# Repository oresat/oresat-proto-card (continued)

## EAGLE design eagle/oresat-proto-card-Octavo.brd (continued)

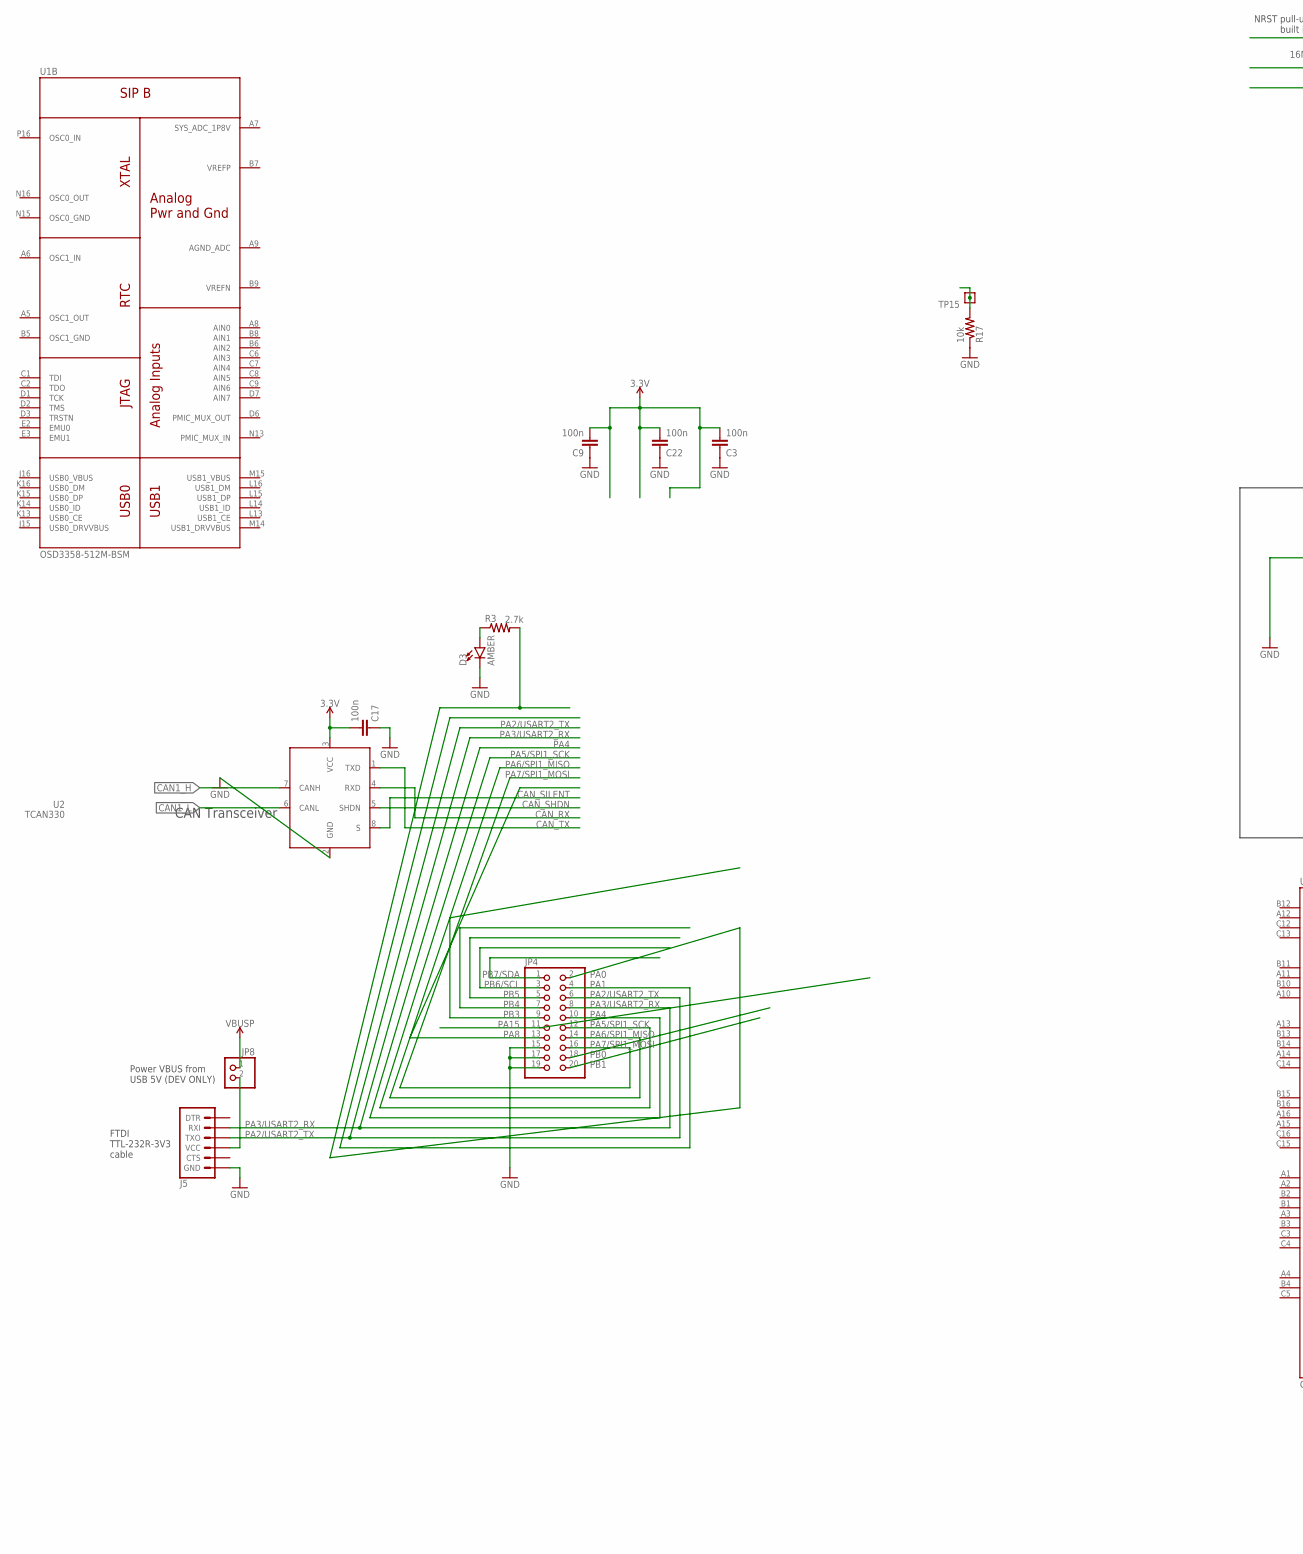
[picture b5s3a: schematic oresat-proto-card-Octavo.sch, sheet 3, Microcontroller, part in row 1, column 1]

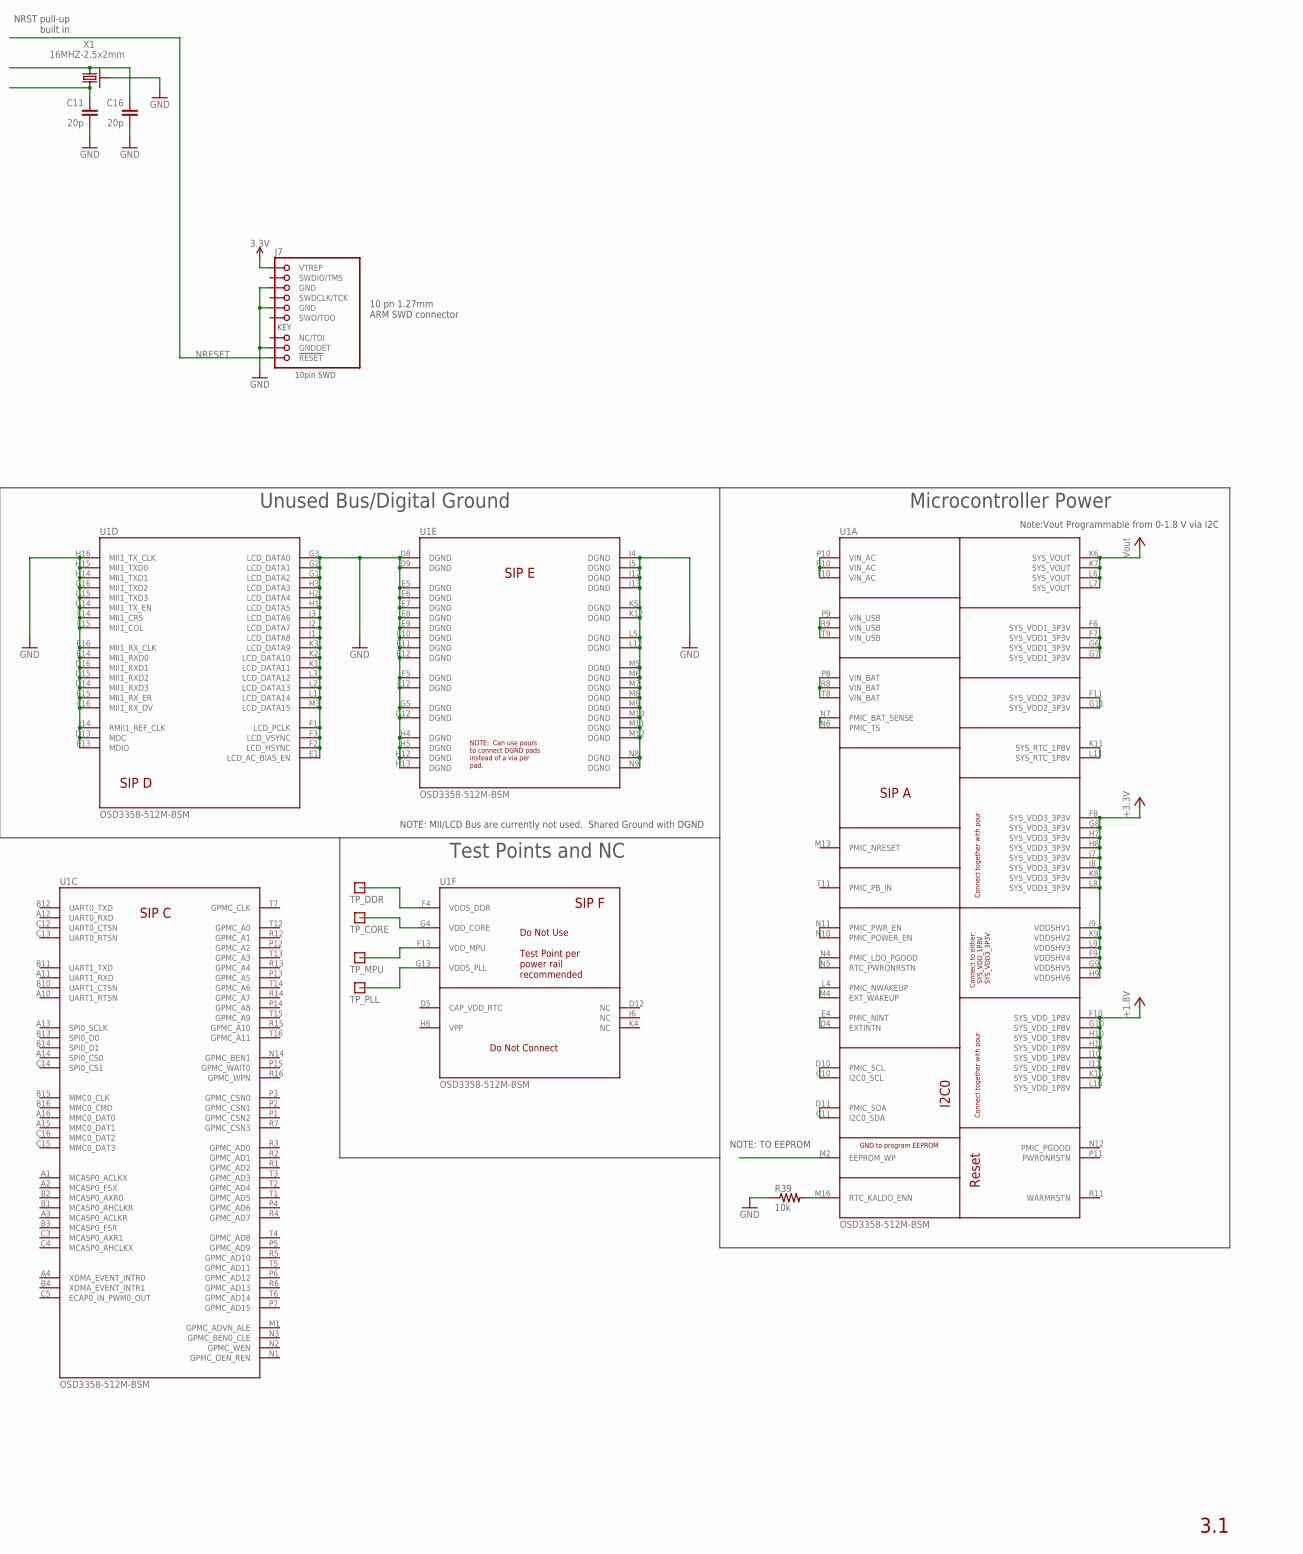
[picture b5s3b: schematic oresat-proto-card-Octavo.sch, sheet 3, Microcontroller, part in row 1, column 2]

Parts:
C3, C9, C17, C22: 100n; .0402-B-NOSILK; MPN CL05B104KO5NNNC
C11, C16: 20p; .0402-B-NOSILK; MPN CL05C200JB51PNC
D3: AMBER; LED-0603
J5: 6_PIN_SERIAL_TARGETSILK; 6_PIN_SERIAL_TARGET_SIDE_W_SILK
J7: FTSH-105-XX-X-DV-K; CON10_2X5_DUK_FTSH; MPN FTSH-105-01-F-DV-K
JP4: PINHD-2X10; 2X10
JP8: PINHD-1X2; 1X02
R3: 2.7k; .0402-B-NOSILK; MPN RC1005F6653CS
R17: 10k; .0402-B-NOSILK; MPN RC1005F6653CS
R39: 10k; R0201
TP15: TEST-POINT; 2MM-TEST-POINT
TP_CORE: TEST-POINT; 2MM-TEST-POINT
TP_DDR: TEST-POINT; 2MM-TEST-POINT
TP_MPU: TEST-POINT; 2MM-TEST-POINT
TP_PLL: TEST-POINT; 2MM-TEST-POINT
U1: OSD3358-512M-BSM; OSD335X-BGA-256
U2: TCAN330; SOT23-8_TI-DCN; MPN TCAN330GDCNT
X1: 16MHZ-2.5x2mm; CRYSTAL_2.5X2; MPN ECS-160-10-36Q-ES-TR

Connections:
3.3V: C3.2, C9.2, C17.2, C22.2, J7.1 (VTREF), U2.3 (VCC); also elsewhere on the board
+3V3: U1.F8 (SYS_VDD3_3P3V), U1.F9 (VDDSHV4), U1.F10 (SYS_VDD_1P8V), U1.G8 (SYS_VDD3_3P3V), U1.G9 (VDDSHV5), U1.G10 (SYS_VDD_1P8V), U1.H7 (SYS_VDD3_3P3V), U1.H8 (SYS_VDD3_3P3V), U1.H9 (VDDSHV6), U1.H10 (SYS_VDD_1P8V), U1.H11 (SYS_VDD_1P8V), U1.J7 (SYS_VDD3_3P3V), U1.J8 (SYS_VDD3_3P3V), U1.J9 (VDDSHV1), U1.J10 (SYS_VDD_1P8V), U1.J11 (SYS_VDD_1P8V), U1.K8 (SYS_VDD3_3P3V), U1.K9 (VDDSHV2), U1.K10 (SYS_VDD_1P8V), U1.L8 (SYS_VDD3_3P3V), U1.L9 (VDDSHV3), U1.L10 (SYS_VDD_1P8V)
BOOT: R17.2, TP15.1
CAN1_H: U2.7 (CANH); also elsewhere on the board
CAN1_L: U2.6 (CANL); also elsewhere on the board
CAN_RX: U2.4 (RXD)
CAN_SHDN: U2.5 (SHDN)
CAN_SILENT: U2.8 (S)
CAN_TX: U2.1 (TXD)
CRYSTALIN: C16.1, X1.1
CRYSTALOUT: C11.1, X1.3 (2)
GND: C3.1, C9.1, C11.2, C16.2, C17.1, C22.1, D3.C, J5.P$6 (GND), J7.3 (GND), J7.5 (GND), J7.9 (GNDDET), JP4.15, JP4.17, JP4.19, R17.1, R39.1, U1.D8 (DGND), U1.D9 (DGND), U1.D13 (MDC), U1.D14 (MII1_RXD3), U1.D15 (MII1_RXD2), U1.D16 (MII1_RXD1), U1.E1 (LCD_AC_BIAS_EN), U1.E5 (DGND), U1.E6 (DGND), U1.E7 (DGND), U1.E8 (DGND), U1.E9 (DGND), U1.E10 (DGND), U1.E11 (DGND), U1.E12 (DGND), U1.E13 (MDIO), U1.E14 (MII1_RXD0), U1.E15 (MII1_RX_ER), U1.E16 (MII1_RX_CLK), U1.F1 (LCD_PCLK), U1.F2 (LCD_HSYNC), U1.F3 (LCD_VSYNC), U1.F5 (DGND), U1.F12 (DGND), U1.F14 (MII1_CRS), U1.F15 (MII1_COL), U1.F16 (MII1_RX_DV), U1.G1 (LCD_DATA2), U1.G2 (LCD_DATA1), U1.G3 (LCD_DATA0), U1.G5 (DGND), U1.G12 (DGND), U1.G14 (MII1_TX_EN), U1.G15 (MII1_TXD3), U1.G16 (MII1_TXD2), U1.H1 (LCD_DATA5), U1.H2 (LCD_DATA4), U1.H3 (LCD_DATA3), U1.H4 (DGND), U1.H5 (DGND), U1.H12 (DGND), U1.H13 (DGND), U1.H14 (MII1_TXD1), U1.H15 (MII1_TXD0), U1.H16 (MII1_TX_CLK), U1.J1 (LCD_DATA8), U1.J2 (LCD_DATA7), U1.J3 (LCD_DATA6), U1.J4 (DGND), U1.J5 (DGND), U1.J12 (DGND), U1.J13 (DGND), U1.J14 (RMII1_REF_CLK), U1.K1 (LCD_DATA11), U1.K2 (LCD_DATA10), U1.K3 (LCD_DATA9), U1.K5 (DGND), U1.K12 (DGND), U1.L1 (LCD_DATA14), U1.L2 (LCD_DATA13), U1.L3 (LCD_DATA12), U1.L5 (DGND), U1.L12 (DGND), U1.M3 (LCD_DATA15), U1.M5 (DGND), U1.M6 (DGND), U1.M7 (DGND), U1.M8 (DGND), U1.M9 (DGND), U1.M10 (DGND), U1.M11 (DGND), U1.M12 (DGND), U1.N8 (DGND), U1.N9 (DGND), U2.2 (GND), X1.2 (SHIELD), X1.4 (SHIELD); also elsewhere on the board
unnamed: D3.A, R3.1
unnamed: U1.F11 (SYS_VDD2_3P3V), U1.G11 (SYS_VDD2_3P3V)
unnamed: U1.N6 (PMIC_TS), U1.N7 (PMIC_BAT_SENSE)
unnamed: U1.K11 (SYS_RTC_1P8V), U1.L11 (SYS_RTC_1P8V)
unnamed: U1.D4 (EXTINTN), U1.E4 (PMIC_NINT)
unnamed: U1.F6 (SYS_VDD1_3P3V), U1.F7 (SYS_VDD1_3P3V), U1.G6 (SYS_VDD1_3P3V), U1.G7 (SYS_VDD1_3P3V)
unnamed: U1.K6 (SYS_VOUT), U1.K7 (SYS_VOUT), U1.L6 (SYS_VOUT), U1.L7 (SYS_VOUT)
unnamed: U1.P10 (VIN_AC), U1.R10 (VIN_AC), U1.T10 (VIN_AC)
unnamed: U1.P9 (VIN_USB), U1.R9 (VIN_USB), U1.T9 (VIN_USB)
unnamed: U1.P8 (VIN_BAT), U1.R8 (VIN_BAT), U1.T8 (VIN_BAT)
unnamed: U1.L4 (PMIC_NWAKEUP), U1.M4 (EXT_WAKEUP)
unnamed: U1.N4 (PMIC_LDO_PGOOD), U1.N5 (RTC_PWRONRSTN)
unnamed: U1.N10 (PMIC_POWER_EN), U1.N11 (PMIC_PWR_EN)
unnamed: U1.C10 (I2C0_SCL), U1.D10 (PMIC_SCL)
unnamed: U1.C11 (I2C0_SDA), U1.D11 (PMIC_SDA)
unnamed: TP_MPU.1, U1.F13 (VDD_MPU)
unnamed: R39.2, U1.M16 (RTC_KALDO_ENN)
unnamed: TP_PLL.1, U1.G13 (VDDS_PLL)
unnamed: TP_CORE.1, U1.G4 (VDD_CORE)
unnamed: TP_DDR.1, U1.F4 (VDDS_DDR)
unnamed: J5.P$4 (VCC), JP8.2
NRESET: J7.10 (!RESET)
PA0: JP4.2, R3.2
PA1: JP4.4
PA2/USART2_TX: J5.P$2 (TXO), JP4.6
PA3/USART2_RX: J5.P$3 (RXI), JP4.8
PA4: JP4.10
PA5/SPI1_SCK: JP4.12
PA6/SPI1_MISO: JP4.14
PA7/SPI1_MOSI: JP4.16
PA8: JP4.13
PA15: JP4.11
PB0: JP4.18
PB1: JP4.20
PB3: JP4.9
PB4: JP4.7
PB5: JP4.5
PB6/SCL: JP4.3
PB7/SDA: JP4.1
VBUSP: JP8.1; also elsewhere on the board

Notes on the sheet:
NRST pull-up built in
FTDI TTL-232R-3V3 cable
Power VBUS from USB 5V (DEV ONLY)
10 pn 1.27mm ARM SWD connector
CAN Transceiver
3.1
NOTE: TO EEPROM
Note:Vout Programmable from 0-1.8 V via I2C
Microcontroller Power
NOTE: MII/LCD Bus are currently not used. Shared Ground with DGND
Unused Bus/Digital Ground
Test Points and NC

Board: 4 copper layers, 118 parts (0 on the bottom side), 96 nets, no tracks yet.

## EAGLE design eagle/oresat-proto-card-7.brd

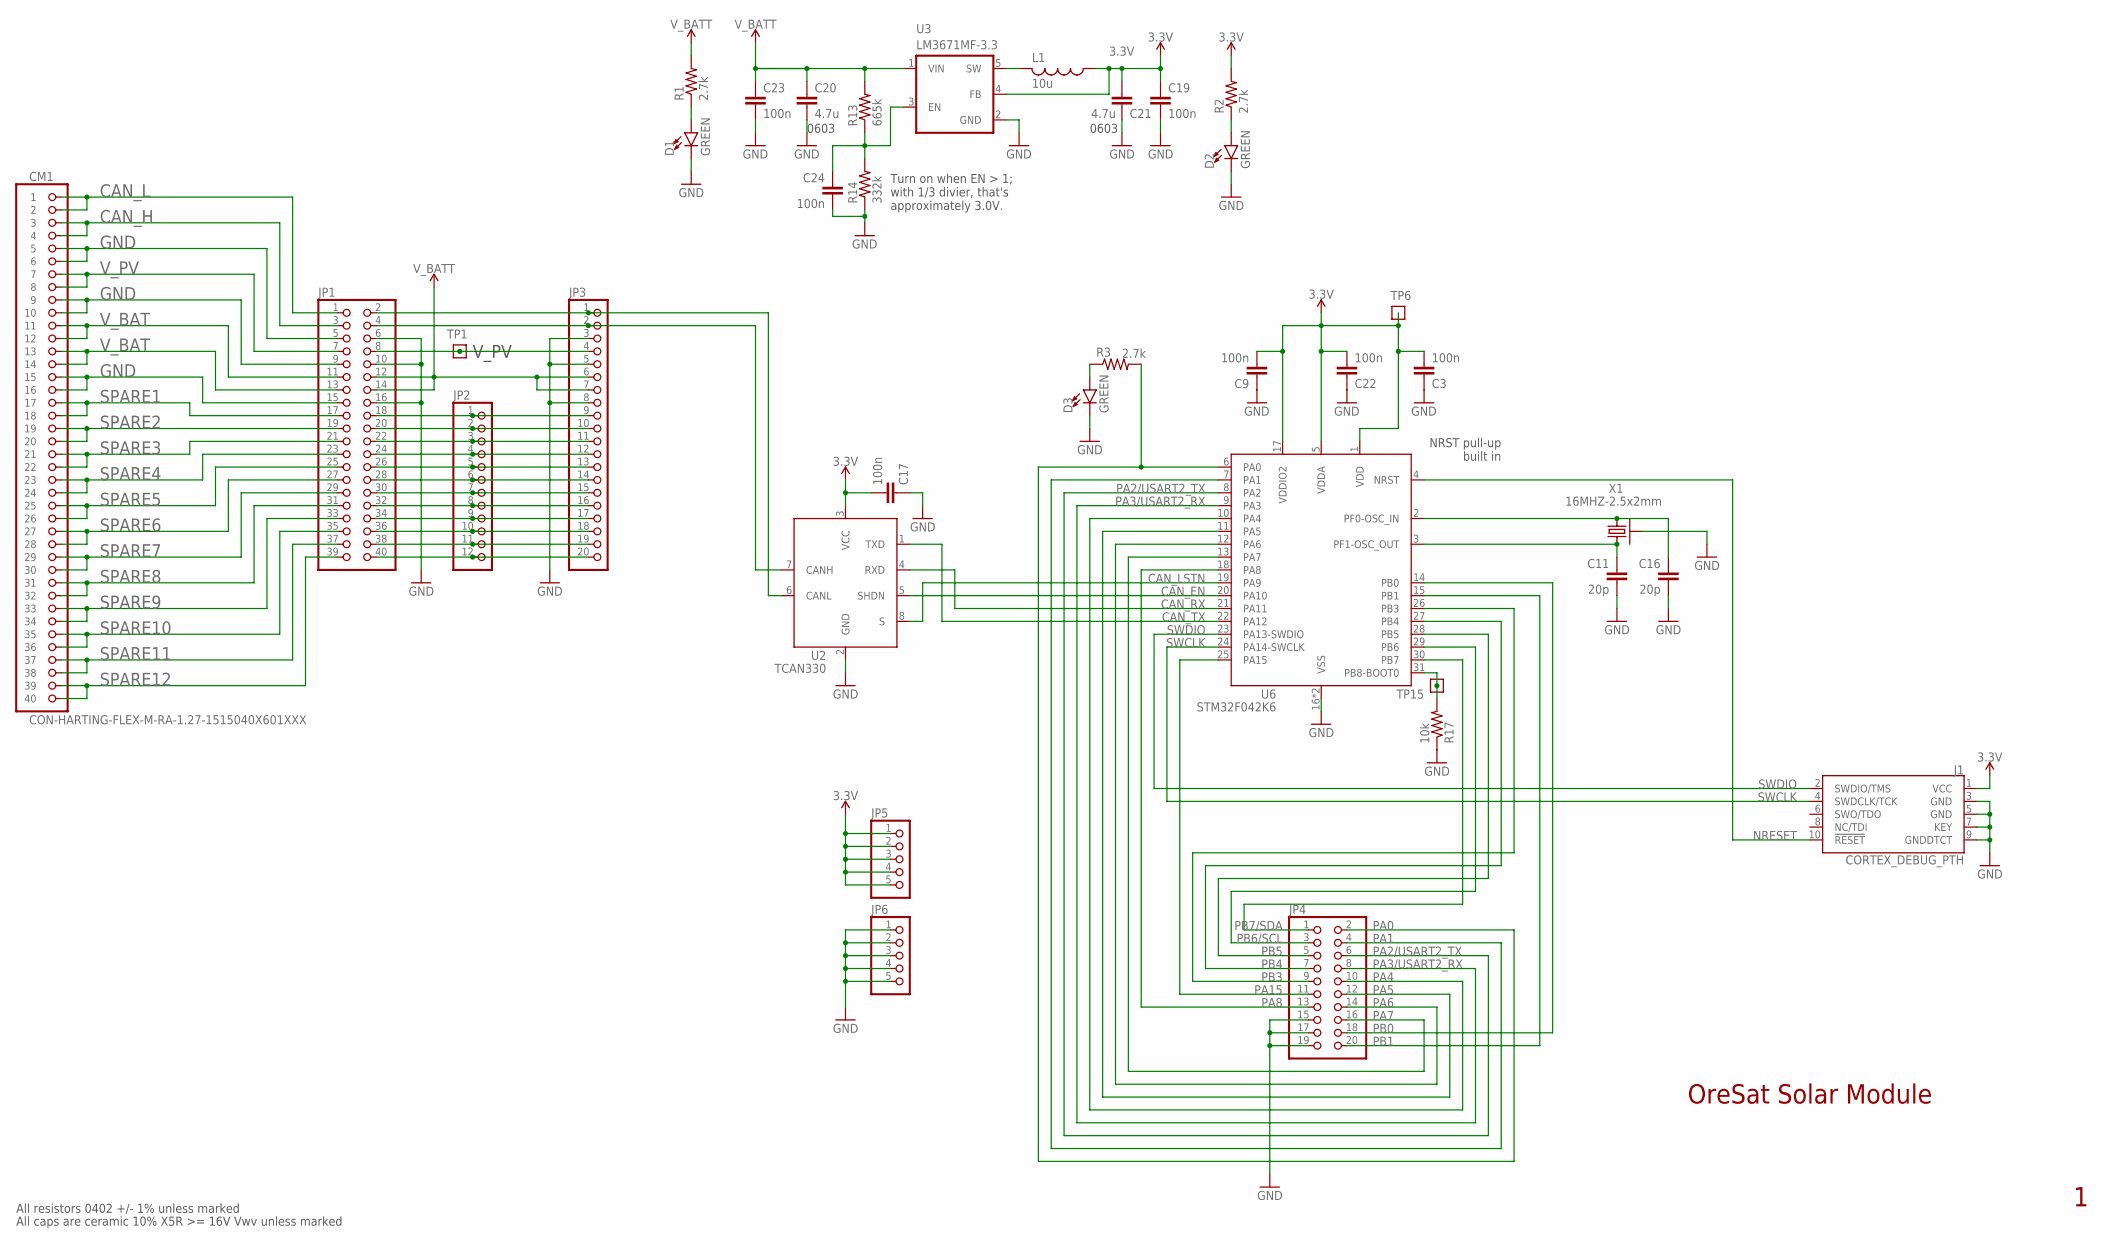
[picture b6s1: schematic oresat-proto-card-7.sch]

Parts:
C3, C9, C17, C19, C22, C23, C24: 100n; .0402-B-NOSILK; MPN CL05B104KO5NNNC
C11, C16: 20p; .0402-B-NOSILK; MPN CL05C200JB51PNC
C20, C21: 4.7u; C0603; MPN CL05B104KO5NNNC
CM1: CON-HARTING-FLEX-M-RA-1.27-1515040X601XXX; CON-1.27-M-RA-HARTING-1515040X601XXX
D1, D2, D3: GREEN; LED-0603
J1: CORTEX_DEBUG_PTH; 2X5-PTH-1.27MM
JP1: PINHD-2X20; 2X20
JP2: PINHD-1X12; 1X12
JP3: PINHD-1X20; 1X20
JP4: PINHD-2X10; 2X10
JP5, JP6: PINHD-1X5; 1X05
L1: 10u; L2012C; MPN CB2012T100KR
R1, R2, R3: 2.7k; .0402-B-NOSILK; MPN RC1005F6653CS
R13: 665k; .0402-B-NOSILK; MPN RC1005F6653CS
R14: 332k; .0402-B-NOSILK; MPN RC1005F3323CS
R17: 10k; .0402-B-NOSILK; MPN RC1005F6653CS
TP1, TP6, TP15: TEST-POINT; 2MM-TEST-POINT
U2: TCAN330; SOT23-8_TI-DCN; MPN TCAN330GDCNT
U3: LM3671MF-3.3; SOT23-5; MPN LM3671MF-3.3/NOPB
U6: STM32F042K6; QFP32-7X7; MPN STM32F042K6T7
X1: 16MHZ-2.5x2mm; CRYSTAL_2.5X2; MPN ECS-160-10-36Q-ES-TR

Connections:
3.3V: C3.2, C9.2, C17.2, C19.1, C21.1, C22.2, J1.1 (VCC), JP5.1, JP5.2, JP5.3, JP5.4, JP5.5, L1.1, R2.2, TP6.1, U2.3 (VCC), U3.4 (FB), U6.1 (VDD), U6.5 (VDDA), U6.17 (VDDIO2)
BOOT: R17.2, TP15.1, U6.31 (PB8-BOOT0)
CANH: JP1.4, JP3.2, U2.7 (CANH)
CANL: JP1.2, JP3.1, U2.6 (CANL)
CAN_EN: U2.5 (SHDN), U6.20 (PA10)
CAN_H: CM1.3, CM1.4, JP1.3
CAN_L: CM1.1, CM1.2, JP1.1
CAN_LSTN: U2.8 (S), U6.19 (PA9)
CAN_RX: U2.4 (RXD), U6.21 (PA11)
CAN_TX: U2.1 (TXD), U6.22 (PA12)
CRYSTALIN: C16.1, U6.2 (PF0-OSC_IN), X1.1
CRYSTALOUT: C11.1, U6.3 (PF1-OSC_OUT), X1.3 (2)
GND: C3.1, C9.1, C11.2, C16.2, C17.1, C19.2, C20.2, C21.2, C22.1, C23.2, C24.2, CM1.5, CM1.6, CM1.9, CM1.10, CM1.15, CM1.16, D1.C, D2.C, D3.C, J1.3 (GND), J1.5 (GND), J1.7 (KEY), J1.9 (GNDDTCT), JP1.5, JP1.6, JP1.9, JP1.10, JP1.15, JP1.16, JP3.3, JP3.5, JP3.8, JP4.15, JP4.17, JP4.19, JP6.1, JP6.2, JP6.3, JP6.4, JP6.5, R14.1, R17.1, U2.2 (GND), U3.2 (GND), U6.16 (VSS), U6.32 (VSS), X1.2 (SHIELD), X1.4 (SHIELD)
unnamed: D3.A, R3.1
unnamed: JP1.8, JP3.4, TP1.1
unnamed: JP1.18, JP2.1, JP3.9
unnamed: JP1.20, JP2.2, JP3.10
unnamed: JP1.22, JP2.3, JP3.11
unnamed: JP1.24, JP2.4, JP3.12
unnamed: JP1.26, JP2.5, JP3.13
unnamed: JP1.28, JP2.6, JP3.14
unnamed: JP1.30, JP2.7, JP3.15
unnamed: JP1.32, JP2.8, JP3.16
unnamed: JP1.34, JP2.9, JP3.17
unnamed: JP1.36, JP2.10, JP3.18
unnamed: JP1.38, JP2.11, JP3.19
unnamed: JP1.40, JP2.12, JP3.20
unnamed: D1.A, R1.1
unnamed: D2.A, R2.1
NRESET: J1.10 (!RESET), U6.4 (NRST)
PA0: JP4.2, R3.2, U6.6 (PA0)
PA1: JP4.4, U6.7 (PA1)
PA2/USART2_TX: JP4.6, U6.8 (PA2)
PA3/USART2_RX: JP4.8, U6.9 (PA3)
PA4: JP4.10, U6.10 (PA4)
PA5: JP4.12, U6.11 (PA5)
PA6: JP4.14, U6.12 (PA6)
PA7: JP4.16, U6.13 (PA7)
PA8: JP4.13, U6.18 (PA8)
PA15: JP4.11, U6.25 (PA15)
PB0: JP4.18, U6.14 (PB0)
PB1: JP4.20, U6.15 (PB1)
PB3: JP4.9, U6.26 (PB3)
PB4: JP4.7, U6.27 (PB4)
PB5: JP4.5, U6.28 (PB5)
PB6/SCL: JP4.3, U6.29 (PB6)
PB7/SDA: JP4.1, U6.30 (PB7)
SPARE1: CM1.17, CM1.18, JP1.17
SPARE2: CM1.19, CM1.20, JP1.19
SPARE3: CM1.21, CM1.22, JP1.21
SPARE4: CM1.23, CM1.24, JP1.23
SPARE5: CM1.25, CM1.26, JP1.25
SPARE6: CM1.27, CM1.28, JP1.27
SPARE7: CM1.29, CM1.30, JP1.29
SPARE8: CM1.31, CM1.32, JP1.31
SPARE9: CM1.33, CM1.34, JP1.33
SPARE10: CM1.35, CM1.36, JP1.35
SPARE11: CM1.37, CM1.38, JP1.37
SPARE12: CM1.39, CM1.40, JP1.39
STEPD: L1.2, U3.5 (SW)
SWCLK: J1.4 (SWDCLK/TCK), U6.24 (PA14-SWCLK)
SWDIO: J1.2 (SWDIO/TMS), U6.23 (PA13-SWDIO)
VDIV: C24.1, R13.1, R14.2, U3.3 (EN)
V_BAT: CM1.11, CM1.12, CM1.13, CM1.14, JP1.11, JP1.13
V_BATT: C20.1, C23.1, JP1.12, JP1.14, JP3.6, JP3.7, R1.2, R13.2, U3.1 (VIN)
V_PV: CM1.7, CM1.8, JP1.7

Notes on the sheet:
NRST pull-up built in
Turn on when EN > 1; with 1/3 divier, that's approximately 3.0V.
OreSat Solar Module
All resistors 0402 +/- 1% unless marked
All caps are ceramic 10% X5R >= 16V Vwv unless marked
0603
V_PV

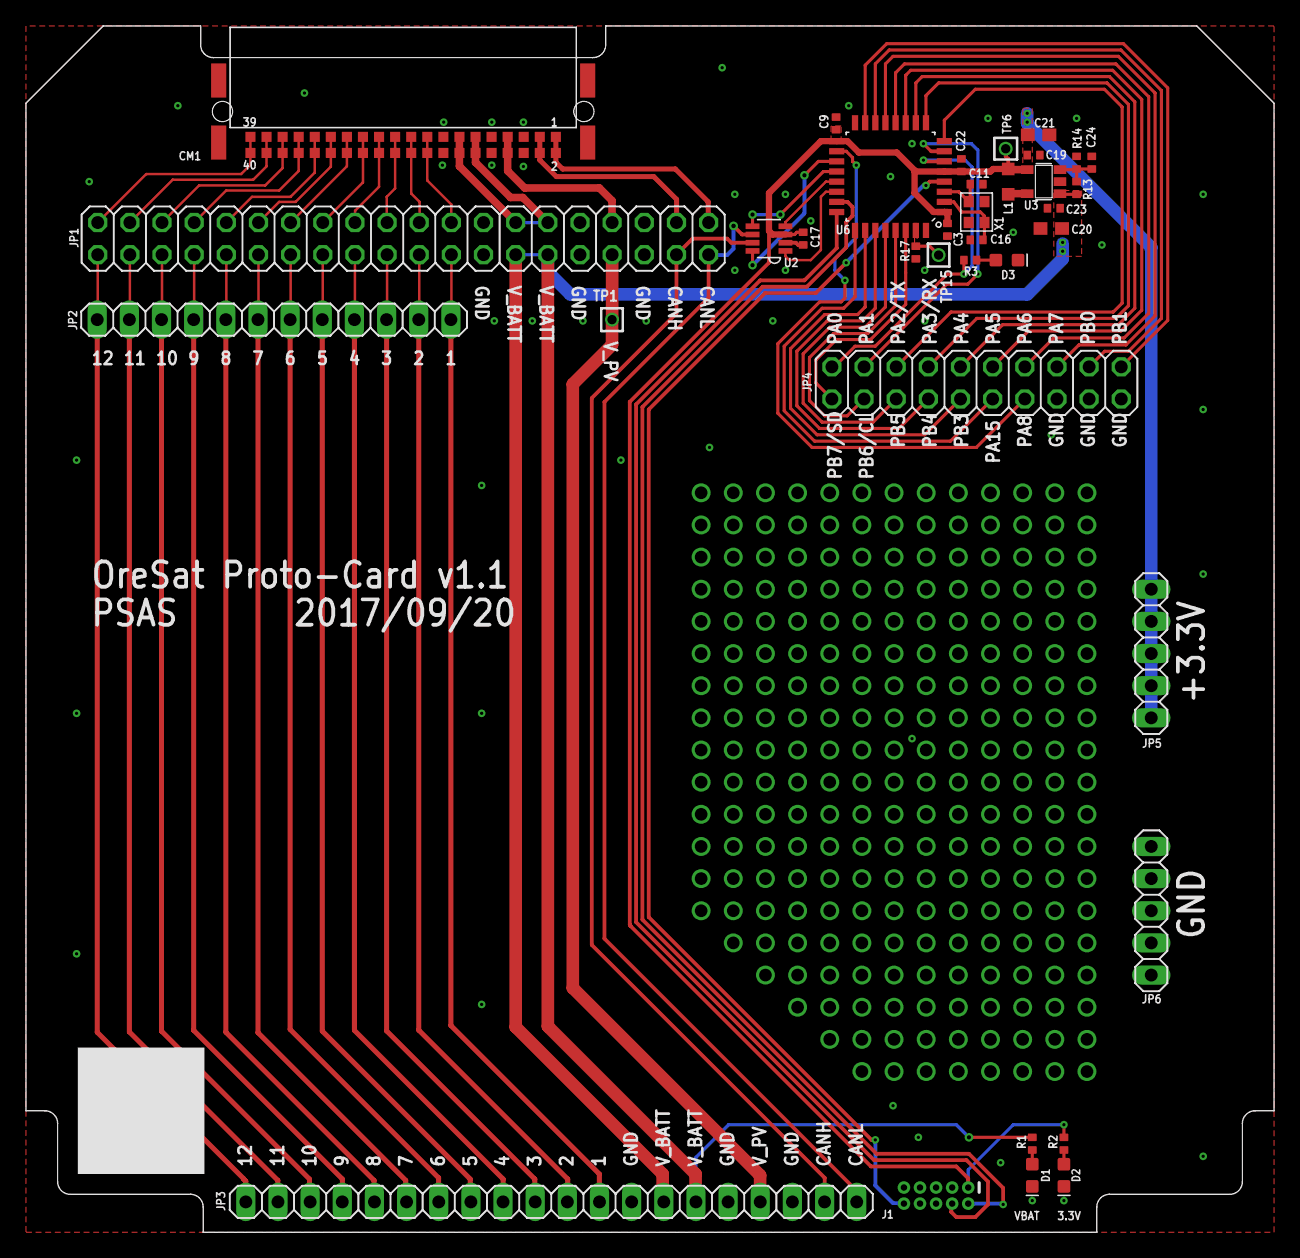
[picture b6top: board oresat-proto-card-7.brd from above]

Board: 2 copper layers, 98.6 x 95.3 mm, 37 parts (0 on the bottom side), 66 nets.

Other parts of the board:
U$1: ORESAT-CARD-V0.5

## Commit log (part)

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2017-09-20 First cut at a protoboard for OreSat.
2017-09-21 Finished protocard layout.
2017-09-21 now with 300% more LEDs!
2017-09-22 Add a pic!
2017-09-22 Oh shoot I forgot text labels. K is going to hate me even more. Well, too late. Ready for v1.1!
2017-09-22 Better smaller pic
2017-09-25 EAGLE 7 files for Austin.
2017-09-28 Minor changes, mostly massaging.
2017-10-01 Still v1.1, but lots of changes! Moved spare lines over, added way more prototyping area, flipped around STM32 to save room, and added 3 MMCX connectors with U.FL breakouts so that we can hook up ext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
2017-10-02 Took K's suggestion: added mounting holes (not necessary in OreSat cards, but whatever) and a FTDI breakout connector. Oh, and stitched some more, and cleaned up silkscreen.
2018-01-10 Updated some net names to reflect SPI bus. Actual useful BOM now.
2018-03-06 Rough draft of the OreSat Prototype Card v2.0! Done, awaiting stapling, TNAMES checking, polish, and feedback from Miles that everything works as expected :)
2018-03-09 Renamed CAN transceiver lines.
2018-03-13 Now with correctly positioned main connector, 100% more auxiliary connectors, and less silly double row headers to make room for it all.
2018-03-13 Removed stupid layers.
2018-03-13 Added DXF import of card outline and keepouts via DXF into the REFERENCE layer. Moved bottom connectors to get out of the way of the fingers from the +X side.
2018-03-13 Added some attributes.
2018-03-13 Cleaned up ERC, changed VBAT to VBUS label.
2018-09-11 Changes for the OreSat Backplane v1.0! Now with 100% more SMPM connectors.
2018-09-11 Recovered BOM which was deleted for some reason. BOM is NOT updated! Needs work.
2018-09-11 Updated protocard documentation.
2018-09-25 Removing GPL v3; moving to CERN OHL.
2018-09-25 Changed to CERN OHL v1.2.
2018-11-22 v3 protocard. Works with current 2018/11/22 structure.
2018-11-22 Update documentation to the latest.
2018-11-22 Huh, image didn't work. Fixed.
2018-11-22 Fixed table.
2018-11-26 minor tweaks, including fixing power supply resistors.
2019-02-10 Uh. Yeah. Well, it wasn't my fault, I blame Oliver J. Power domain circuitry now figured out from a topology point of view. Lots of changes to the power front end, and the main and aux connctors. Als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
2019-02-10 Cleaned up TNAMES layer.
2019-02-10 More schematic and board polishing. Went over ERCs and DRCs, some layout polishing, more ground stitching.
2019-02-11 More board and schematic polishing. Swapped SWD connector with SMT version for easy removal. Added more test points on the MAX7210 power domain controller.
2019-02-25 Latest OreSat protocard, version 3.1, with updated BOM, and design notes!
2019-02-25 Ugggh digikey made me add their part numbers. Hrmph.
2019-02-27 Added OreSat power domain -- via design blocksgit status -- and OMG it's doneish.
2019-02-27 OMG next time check which repo you're in. Reverting the last commit and push.
2019-03-27 Added new safety circuit on the I2C of the OPD.
2019-05-22 Latest card outline from Ryan and Catie, and added the first OPD protection circuit revision.
2019-06-24 uploading very early octavo protocard stuff
2019-07-09 Made note of error in circuit breaker to be fixed at a later date
2019-07-17 flipped comparator inputs on circuit breaker
2019-07-18 updated m0 protocard to include I2C breaker CAD and added more stitching
2019-07-18 removed TODO note
2019-07-20 added datasheets for m0
2019-07-29 last minute drc fixes
2019-07-29 fixed airwire
2019-07-30 added capablity for M0 bootstrapping over OPD I2C bus. Added extra ground plane stitching. Replaced some previously removed prototyping area
2019-07-31 moved some stitching around
2019-08-03 Final cleanup on the v3.2 protocard. Moved tall components away from the +X end of things because of the new slopes on the +X frame, and added two resistors on the OPD I2C bootloader gambit because w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
2019-08-04 OMG that was close: Changes to main pinout in Backplane v2.1 did not get updated in protocard. Fixed.
2019-08-04 flatsat breakout boards, one for main, one for aux, connectors.
2019-08-04 More notes after talking with David, changed I2C bootloader resistor values, and fixed AUX conector signal names.
2019-08-05 Moved in +X squeezy ends by 0.15 mm on both sides.
2019-08-05 Reduce all vias to 0.254 mm.
2019-08-05 TPLACE cleaup.
2019-08-12 added todo on protocard to connect Iout and Pout to M0
2019-08-20 "auto-generated from update_repos.py"
2019-08-25 added test point on the nreset line
2019-08-25 added test point to cb_ctrl
2019-09-02 added test points and updated manufacturing image
2019-09-04 added SPICE simulations for the I2C protection circuit
2019-09-16 updates to OPD, new I2C protection circuit
2019-09-28 Added new I2C protection, connected Pout to M0 through 10k
2019-10-29 added board layout of new I2C protection circuit
2019-10-29 stray airwire
2019-12-07 fixed j-tag connect, final tweaks for 3.3, updated bom
2019-12-17 Now v3.3. New OPD I2C protection circuits. Move to 4 layers. Lots of cleanup and massaging, but nothing worth saying. Added ground ring around 3.3V ring on L15. Attributes are still wrong, needs to b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
2019-12-20 Removed lockfile. Nice one, David.
2019-12-20 fixing the lock?
2019-12-20 organization house keeping
2019-12-23 Fixed MIC842L flipped pins. Layout turned out to be better, too!
2020-02-27 Added card debug board
    20 pin ffc edge connector debug board
2020-02-27 Design and layout notes For Debug board
2020-02-27 Added lables, diff pairs , GND vias
2020-02-28 Added P Channel MOSFET switched VUSB
    Made Voltage buses wider
2020-02-28 Added jumper select for Host5V or Debug-0
2020-02-28 Clear stubs and DRC errors
2020-02-28 clear all ERC errors
2020-02-28 Push For Review
2020-02-28 Minor fixes
    Added labels
2020-02-29 Design review changes made
2020-03-03 Made changes per design review
    Added test points for RX TX rewire, made board smaller
2020-03-16 Added masking for TX and RX
2020-03-25 Changed from VBUSP to VBUS for power out
2020-04-14 Swapped TX RX traces
2020-04-14 updated the pin connectors
2020-04-20 Version 1 of the OreSat debug board. Tinyified the board, added curved corners, centered FFC connector, added reset switch, made USB traces have a continuous ground plane, fixed FT203x VCCIO connecti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
2020-04-27 Renamed VBUS to VBUSP added attributes to make BOM
2020-04-27 Completed Version 1 BOM for connector board
2020-05-24 Re-Done with mirrored edge connector
2020-05-24 Clean up text , added gnd via's
2020-06-21 protocard preliminary rev 3.5
2020-06-22 new stm dbl, new programming connector, minor layout tweaks
2020-06-25 swapped 0402 to 0603 where necessary, fixed labels on tnames layer
2020-06-28 updated design blocks, got rid of unneeded breakouts
2020-06-28 Polishing to the schematic only; ready for v4! Still needs layout polishing.
2020-06-29 Switched to thin mirrored edge connector
2020-06-29 moved ffc to bottom of card, fixed silkscreen, moved and expanded Vbus and 3.3V breakouts
2020-06-30 minor tweak to ground plane stitching
2020-07-06 Added jumper and diode for 3.0V supply for solar for debugging without solar power.
2020-07-06 fixed an error where Pout was not routed to an ADC pin
2020-07-20 Minor DRC clean up, fixed 3.3V plane cut by VBUSP, and some TSTOPs being too close.
2020-07-20 Minor erc and drc cleanup.
2020-07-22 updated attributes and BOM
2020-08-09 Added 10k resistor to the FTDI's TXD line so that we don't accidentally power the card through the transmit line)
2020-08-09 Fixed RX/TX screw up (updated debug connector).
2020-08-10 Updated to 4.1: switched to better debug connector, fixed OPD capacitance problem.
2020-08-10 Oh right and fix the I2C pullups to 4.7k
2020-12-02 Added 10 uF cap after on/off P channel switch, and added values to MAX4311 inhibit RC circuitr, all to prevent accidental trips.
2020-12-02 Added MAX4311 inhibit RC filter calculations.
2021-08-22 Moved design notes to a google document, and linked it.
2021-08-29 Moved debug and card breakouts to the oresat-flatsat repo.
2021-10-31 Fixed a handful of misc Git issues. Started KiCAD import of protocard V4.1
2021-11-09 moved files to f0-proto-card folder
2021-11-11 imported oresat-live-card Eagle project to KiCAD 5.99. Moved oresat-proto-card files to f0-proto-card directory
2021-11-15 removed page 6; edited connectors, PWR and SD reader schematic
2024-02-09 Updated proto card to new board outline and backplane pinout. Moved to KiCAD
2024-02-25 Some design review changes for protocard v5.0
2024-02-25 Finished cleaning up protocard
2024-03-22 Starting to correctly name all the protocards
2024-03-22 Latest .gitignore file
2024-03-22 Removed temporary files that shouldn't have been committed.
2024-03-22 More cleanup, and renaming of files, and better page layout
2025-06-29 Set up new folder for MCXN version of the protocard
2025-06-30 Replaced J1 and JP9 w/ OreSat library equivalent
2025-06-30 Removed and replaced eagle libraries for C, R, and Power symbols
2025-07-02 Removed and replaced Eagle libraries for MOSFET
2025-07-03 Eagle libraries removed and replaced, schematic and layout clean up
2025-07-08 Eagle libraries replaced, scheatic and layout clean up cont.
2025-07-08 Cleaned up layout and routing
2025-07-08 Updated TPS62111RSA
2025-07-09 changed layout
2025-07-11 Fixed linked library footprints and routing
2025-07-12 Fixed schematic and routing for 2x11 connector
2025-07-14 Fixed some minor ERC and DRC errors
2025-11-19 Fully routed MCXN947 proto card, still needs final polish.
    Big cleanup of the proto card's OPD, bringing it up to modern standards. Also fixed the v2 backplane connector. Added the MCXN937 processor, and breakouts for the unused pins. Switched to the new deb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
2025-12-29 Final MCXN protocard cleanup
    Made schematic fancy with hierarchical pins, cleaned up schematics a bit, and fixed silk screen a ton. Ready for fab.
2025-12-29 Fab v6.0 proto-card
2025-12-30 BOM fixed; schematic polish (no change to PCB v6.0)
    Fixed BOM, and synced with OreSat BOMs Google Sheet. Figured out large capacitor (> 4.7u) voltages and package issues, which are many. Set MCXN pin names to the right selection if possible.
2025-12-30 Small schematic aesthetics, no change to sch or pcb.
2026-06-28 Update protocard
    Update to 10.0.4, new .gitignore, better hierachical layout, updated footprints, re-arranged LEDs, brought outline and SMPMs into latest standards, all but OPD is updated.
2026-06-29 Small cleanups for manufacturing
